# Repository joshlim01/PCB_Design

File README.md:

# PCB-Design

### Files:
- PCB Course Certificate : A certificate showing completion of 30 hour PCB design course
- pcbDesign.kicad_pcb : PCB layout file in KiCAD
- signalGeneratorGerber.zip : Gerber files
- Pictures folder contains photos of the PCB design, KiCAD layout, and finished soldered board

### Description:

A signal generator PCB design project performed as part of a 30 hour course through the UBC PHAS Elab, Fall 2022.  A 15V DC signal is passed through a voltage regulator to produce 5V DC.  The 5V is passed through a 5V -> -5V converter to power the rails of an op-amp that can control output signal amplitude.  5V powers a 100kHz Timer/Oscillator that produces a squarewave signal that can be tuned in combination with the potentiometers and the op-amp.  Tuned signal can be read from a through-hole test port.

Project phases included:

#### Design
- Creating a schematic in EDA software (KiCad), including additions to the parts library.
- Creating custom component footprints to match manufacturer specifications.
- Review of good design priciples for PCB circuit layout.
- Manual layout of circuit onto a two-layer PCB, design rules specifications, variable width traces.
- Custom silk screen layering, sizing, and drill holes for ease of assembly.
- Gerber file production and PCB ordering.

#### Assembly
- Manual soldering of surface mount components with a Soldering Iron Kit.
- Testing and validation with digital oscilloscope and multimeter.

### Youtube Video:

I also documented the soldering experience with a fun video and timelapse montage on Youtube. Feel free to watch it here: https://youtu.be/N-I3tIIquEQ?si=bvdNDSMJbE_GzZRB

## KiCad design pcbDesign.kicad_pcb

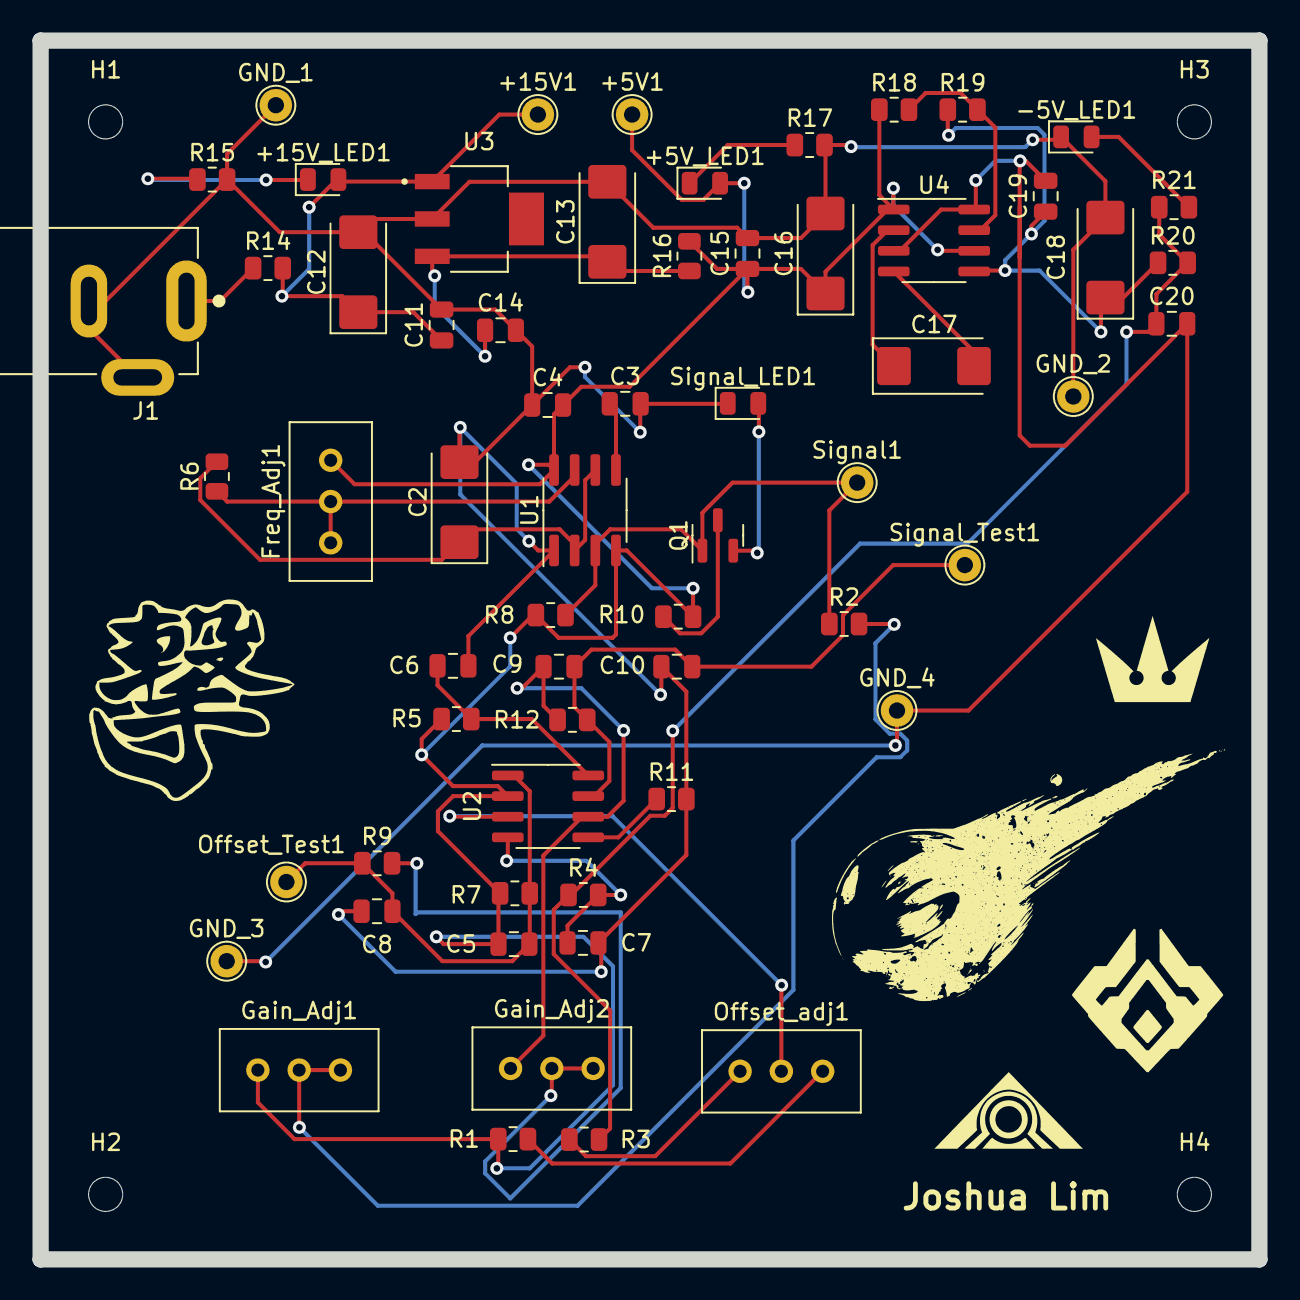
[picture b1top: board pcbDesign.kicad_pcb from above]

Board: 2 copper layers, 75.0 x 75.0 mm, 66 parts (0 on the bottom side), 31 nets.

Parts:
+5V1, +15V1: Test Point; TestPoint_THTPad_D2.0mm_Drill1.0mm
+5V_LED1, +15V_LED1: LED; LED_0805_2012Metric
-5V_LED1: LED; LED_0805_2012Metric
C2, C12, C13, C16, C17, C18: 10u; CP_EIA-6032-15_Kemet-U
C3, C4, C6, C7, C10, C11, C14, C15, C19, C20: 10n; C_0805_2012Metric
C5, C9: 22p; C_0805_2012Metric
C8: DNP; C_0805_2012Metric
Freq_Adj1: 100K; Potentiometer_Bourns_3296W_Vertical
GND_1, GND_2, GND_3, GND_4: Test Point; TestPoint_THTPad_D2.0mm_Drill1.0mm
Gain_Adj1, Gain_Adj2: 100K; Potentiometer_Bourns_3296W_Vertical
H1, H2, H3, H4: MountingHole; MountingHole_2.1mm
J1: Barrel_Jack_Switch; CUI_PJ-002A
Offset_Test1: Test Point; TestPoint_THTPad_D2.0mm_Drill1.0mm
Offset_adj1: 100K; Potentiometer_Bourns_3296W_Vertical
Q1: DMN10H700S; SOT-23
R1, R2, R3, R9: 1K; R_0805_2012Metric
R4, R5: 1R; R_0805_2012Metric
R6, R7, R12: 10K; R_0805_2012Metric
R8: 100R; R_0805_2012Metric
R10, R17, R21: 150R; R_0805_2012Metric
R11: 25K; R_0805_2012Metric
R14, R16, R20: 0R; R_0805_2012Metric
R15: 650R; R_0805_2012Metric
R18, R19: 100K; R_0805_2012Metric
Signal1: Test Point; TestPoint_THTPad_D2.0mm_Drill1.0mm
Signal_LED1: LED; LED_0805_2012Metric
Signal_Test1: Test Point; TestPoint_THTPad_D2.0mm_Drill1.0mm
U1: NE555D; SOIC-8_3.9x4.9mm_P1.27mm
U2: AD8039; SOIC-8_3.9x4.9mm_P1.27mm
U3: LM7805_TO220; VREG_LM7805MPX_NOPB
U4: MAX889; SOIC-8_3.9x4.9mm_P1.27mm

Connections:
5V: +5V1.1, +5V_LED1.2 (A), C4.2, C5.1, C15.1, C16.1, Freq_Adj1.1, Gain_Adj1.3, R1.1, R5.1, R7.1, R8.1, R10.2, R16.2, R18.1, U1.4 (R), U1.8 (VCC), U2.2 (-), U4.1, U4.6
-5V: C20.1, R3.2, R4.1, R20.2, R21.1
GND: -5V_LED1.1 (K), C2.2, C3.2, C4.1, C6.2, C7.2, C8.1, C10.1, C11.2, C12.2, C13.2, C14.2, C15.2, C16.2, C18.2, GND_1.1, GND_2.1, J1.2, J1.3, R11.2, R15.2, R17.2, Signal_LED1.1 (K), U1.1 (GND), U3.2 (GND)
unnamed: +5V_LED1.1 (K), R17.1
unnamed: +15V1.1, +15V_LED1.2 (A), C11.1, C12.1, R14.2, U3.1 (VI)
unnamed: +15V_LED1.1 (K), R15.1
unnamed: -5V_LED1.2 (A), R21.2
unnamed: C2.1, R6.2, U1.2 (TR), U1.6 (THR)
unnamed: C3.1, U1.5 (CV)
unnamed: C5.2, C8.2, Offset_Test1.1, R7.2, R9.1, U2.1
unnamed: C6.1, R5.2, U2.8 (V+)
unnamed: C7.1, R4.2, U2.4 (V-)
unnamed: C9.1, Gain_Adj2.3, R12.1, U2.6 (-)
unnamed: C9.2, C10.2, R12.2, Signal_Test1.1, U2.7
unnamed: C13.1, C14.1, R16.1, U3.3 (VO)
unnamed: C17.1, U4.2
unnamed: C17.2, U4.4
unnamed: C18.1, C19.1, R19.1, R20.1, U4.5
unnamed: C19.2, C20.2, GND_3.1, GND_4.1, U4.3, U4.8
unnamed: Freq_Adj1.2, Freq_Adj1.3, R6.1, U1.7 (DIS)
unnamed: Gain_Adj1.1, Gain_Adj1.2, R2.2
unnamed: Gain_Adj2.1, Gain_Adj2.2, R9.2
unnamed: J1.1, R14.1
unnamed: Offset_adj1.1, R1.2
unnamed: Offset_adj1.2, U2.3 (+)
unnamed: Offset_adj1.3, R3.1
unnamed: Q1.1 (G), R2.1, R8.2, Signal1.1, U1.3 (Q)
unnamed: Q1.2 (S), Signal_LED1.2 (A)
unnamed: Q1.3 (D), R10.1
unnamed: R11.1, U2.5 (+)
unnamed: R18.2, R19.2, U4.7

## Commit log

2025-03-02 cleaned up repo
2025-03-02 Added pictures to README
2025-03-02 Fixed README again
2025-03-02 Included yt video
